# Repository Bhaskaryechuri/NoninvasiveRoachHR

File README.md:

_Author: [Bhaskar Yechuri](bhaskar.yechuri@gmail.com), Engineering Technician & Research Assistant at the [Phil Matthews Lab](http://www.matthewslab.zoology.ubc.ca/index.html), University of British Columbia - Vancouver (Last Updated: June 2021)_

# Non-Invasive Cockroach Heart Rate Monitor
A device &amp; method developed to non-invasively measure cockroach heart rate of a free-roaming cockroach.

# Summary

This photoplethysmographic device, inspired by the methods of [this paper](https://aslopubs.onlinelibrary.wiley.com/doi/abs/10.4319/lom.2013.11.91) and mounted directly onto the roach's sclerites, uses infrared LEDs and two phototransistors (i.e. IR sensors) to noninvasively monitor cockroach heart rate in real-time. [Here is a video of it in action](https://drive.google.com/file/d/15U84yjhjsBKMVfOA489h0GwnW5KllRH3/view?usp=sharing).

The system consists of the following components:
* [3D-Printed Mount](https://github.com/Bhaskaryechuri/NoninvasiveRoachHR/tree/main/mechanical): A plastic structure attached to the roach's back along the midline using melted bikini wax. This structure firmly holds the mini-PCB's LEDs & sensors close to the roach's sclerites.
* [mini-PCB](https://github.com/Bhaskaryechuri/NoninvasiveRoachHR/tree/main/circuit): Placed on the roach via the 3D-printed mount. Contains the LEDs and sensors that allow for heart rate sensing, and a symmetrical 5-pin header which can be used to conduct sensor signals out of the board and power in (GND-Signal1-5V-Signal2-GND)
* Auxiliary Board: A simple circuit connecting to the mini-PCB via a 5-pin ribbon cable, routing the outgoing signals to two independent BNC outputs and connecting the 5V power supply terminals to the mini-PCB

# Fabrication & Assembly

This section contains information on how to assemble the device from scratch.

_NOTE: If you are working with an already-fabricated device, you can skip this step._  

**Mini-PCB**:

1. From the `circuit` folder in this repository, download the ".SCH" and ".BRD files" and open them in [AutoCAD EAGLE](https://www.autodesk.ca/en/products/eagle/free-download)
2. Navigate to the board-view and click "ratsnest", which will create the ground plane
3. The simplest way to create the PCB would be to order it from a third-party PCB manufacturer (e.g. PCBWay, JLPCB, etc.), which are cheap, have a relatively short turnaround time, and minimize human error when compared to milling it using the CNC. To do this, each manufacturer requires a set of auto-generated outputs from EAGLE. If you get the PCBs manufactured externally, skip to Step 6
4. Export the .GBR and .XLN files and use those along with [FlatCAM](http://flatcam.org/) (only works on Windows) to generate CNC gcode files
5. Use the gcode files to mill out PCBs using the Carbide CNC machine
    1. It is recommended to try a few test runs on the CNC machine with used/scrap PCBs
6. Once the PCBs are ready, solder on the components according to the schematic & layout seen in the EAGLE files
7. Use heatshrink tubing to neatly seal the area around the LEDs to prevent light leaking out from the sides and into the adjacent sensors. Snip off the top of the tubing to ensure that only the sides of the LEDs are obscured, not the tops

**3D-printed mount**:

1. From the `mechanical` folder in this repository, download the ".STL" file and open it in [Ultimaker Cura](https://ultimaker.com/software/ultimaker-cura)
2. Align the flat surface of the mount to the build plate in Ultimaker Cura, choose the appropriate printer type, and set the infill to 100% with the ABS material
3. Click the "Slice" button and look at the "Preview" tab to ensure that the smaller features of the mount will be printed. If not, modify the print settings
4. Finally, save the gcode produced by the Ultimaker Cura to a flash drive and plug the drive into the lab 3D printer. Ensure that the material installed is ABS and print the file

**Auxiliary Board**:

1. Solder another 5-pin female header into a proto-board and connect additional jumpers to route the outer pins to their appropriate connections    
    1. (1 and 5) to GND, 
    2. the center pin (3) to 5V, and 
    3. the middle pins (2 and 4) to independent BNC outputs (i.e. signal1 and signal2)
1. During experiments, connect the BNC cables to this auxiliary board and the power supply terminals to the appropriate locations on the board. Do not leave the power supply connected when not in use.

# Usage Instructions

Once you have an assembled device ready to use, follow these steps to successfully read a heart rate signal from a cockroach:
1. First, test the electrical parts by connecting the mini-PCB and auxiliary board with the 5-pin ribbon cable. Connect the BNC outputs to a data logging program (e.g. LabChart + PowerLab), and connect the 5V power supply to the auxiliary board
    1. To test whether the sensors and LEDs are working as expected, place a sheet of paper in front of the LEDs and sensors to see whether the sensor voltage decreases on your computer screen. This shows that the LEDs are shining light outward, which then is reflecting back onto the sensors, resulting in the sensor voltage reacting accordingly. Make sure to unplug the power supply when you are done testing!
1. Attach the mini-PCB onto the mount in a secure but reversible way. A small amount of transparent, residue-free tape works well
2. Next, narcotize the cockroach using CO2 for ~30s. This will immobilize it for a few minutes to allow for easy mounting of the mount and board
3. Microwave bikini wax until it has the consistency of honey (but ensure it is not hot enough to burn your skin or the cockroach) and use it to attach the 3D printed mount onto the third sclerite of the cockroach. Use the "wings" of the mount as the wax attachment surfaces, to ensure that the sensors and LEDs are not obscured by wax and to make them fit flush with the surface of the sclerite. Ensure that the sensors and LEDs are aligned with the midline of the roach, on the roach's 3rd sclerite
4. Once the mount and mini-PCB are attached firmly to the roach, connect the mini-PCB to the auxiliary board using the 5-pin ribbon cable. Finally, connect the auxiliary board to the power supply. As the cockroach slowly wakes up from being narcotized, the two signals should slowly become visible on your computer screen. It helps to manually rescale the axes on the screen to zoom into the heart rate signals being produced. Signals will typically range from 2-20mV in amplitude (peak-to-peak), depending on how closely your sensors and LEDs are to the surface of the roach

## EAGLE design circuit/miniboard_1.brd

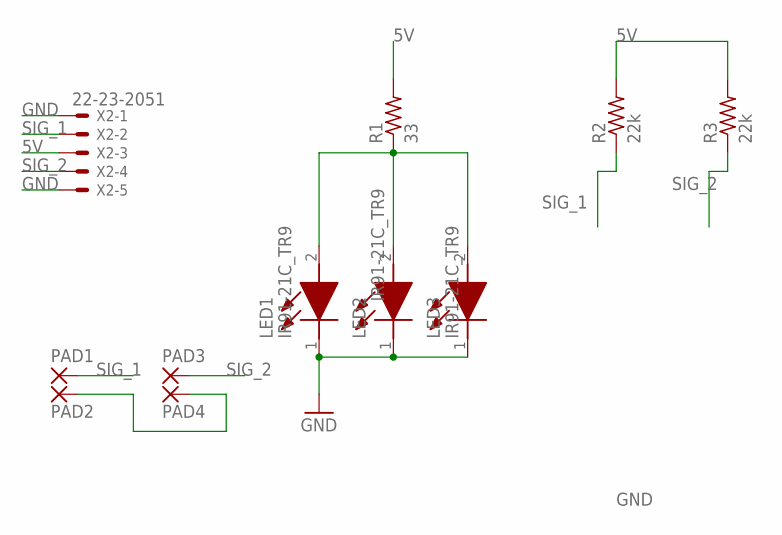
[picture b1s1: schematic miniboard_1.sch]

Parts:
LED1, LED2, LED3: IR91-21C_TR9; SODFL7422X280N
PAD1, PAD2, PAD3, PAD4: SMD2; SMD1,27-2,54
R1: 33; 0204/5
R2, R3: 22k; 0204/5
X2: 22-23-2051

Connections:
5V: R1.2, R2.2, R3.2, X2.3
GND: LED1.1 (K), LED2.1 (K), LED3.1 (K), PAD2.1, PAD4.1, X2.1, X2.5
unnamed: LED1.2 (A), LED2.2 (A), LED3.2 (A), R1.1
SIG_1: PAD1.1, R2.1, X2.2
SIG_2: PAD3.1, R3.1, X2.4

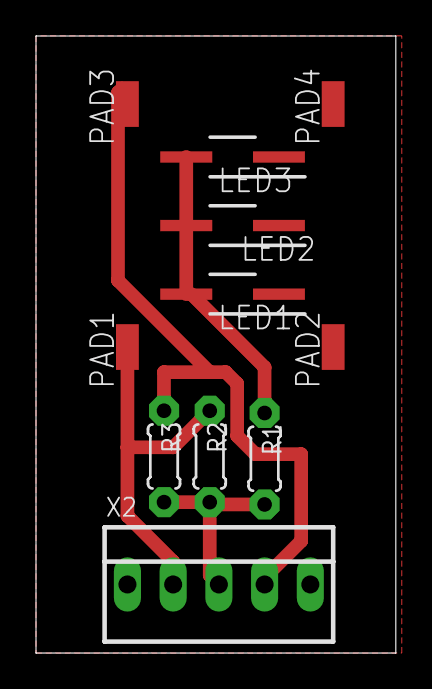
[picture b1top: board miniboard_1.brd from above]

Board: 2 copper layers, 20.0 x 34.3 mm, 11 parts (0 on the bottom side), 5 nets.

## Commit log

2021-06-08 Create test
2021-06-08 Add files via upload
    Solidworks file (editable) + STL file (printable through Ultimaker Cura) for the Cockroach-Mounted piece
2021-06-08 Add files via upload
    uploading pcb design files
2021-06-08 Add files via upload
    All files pertaining to previous iterations are uploaded here for reference/posterity.
